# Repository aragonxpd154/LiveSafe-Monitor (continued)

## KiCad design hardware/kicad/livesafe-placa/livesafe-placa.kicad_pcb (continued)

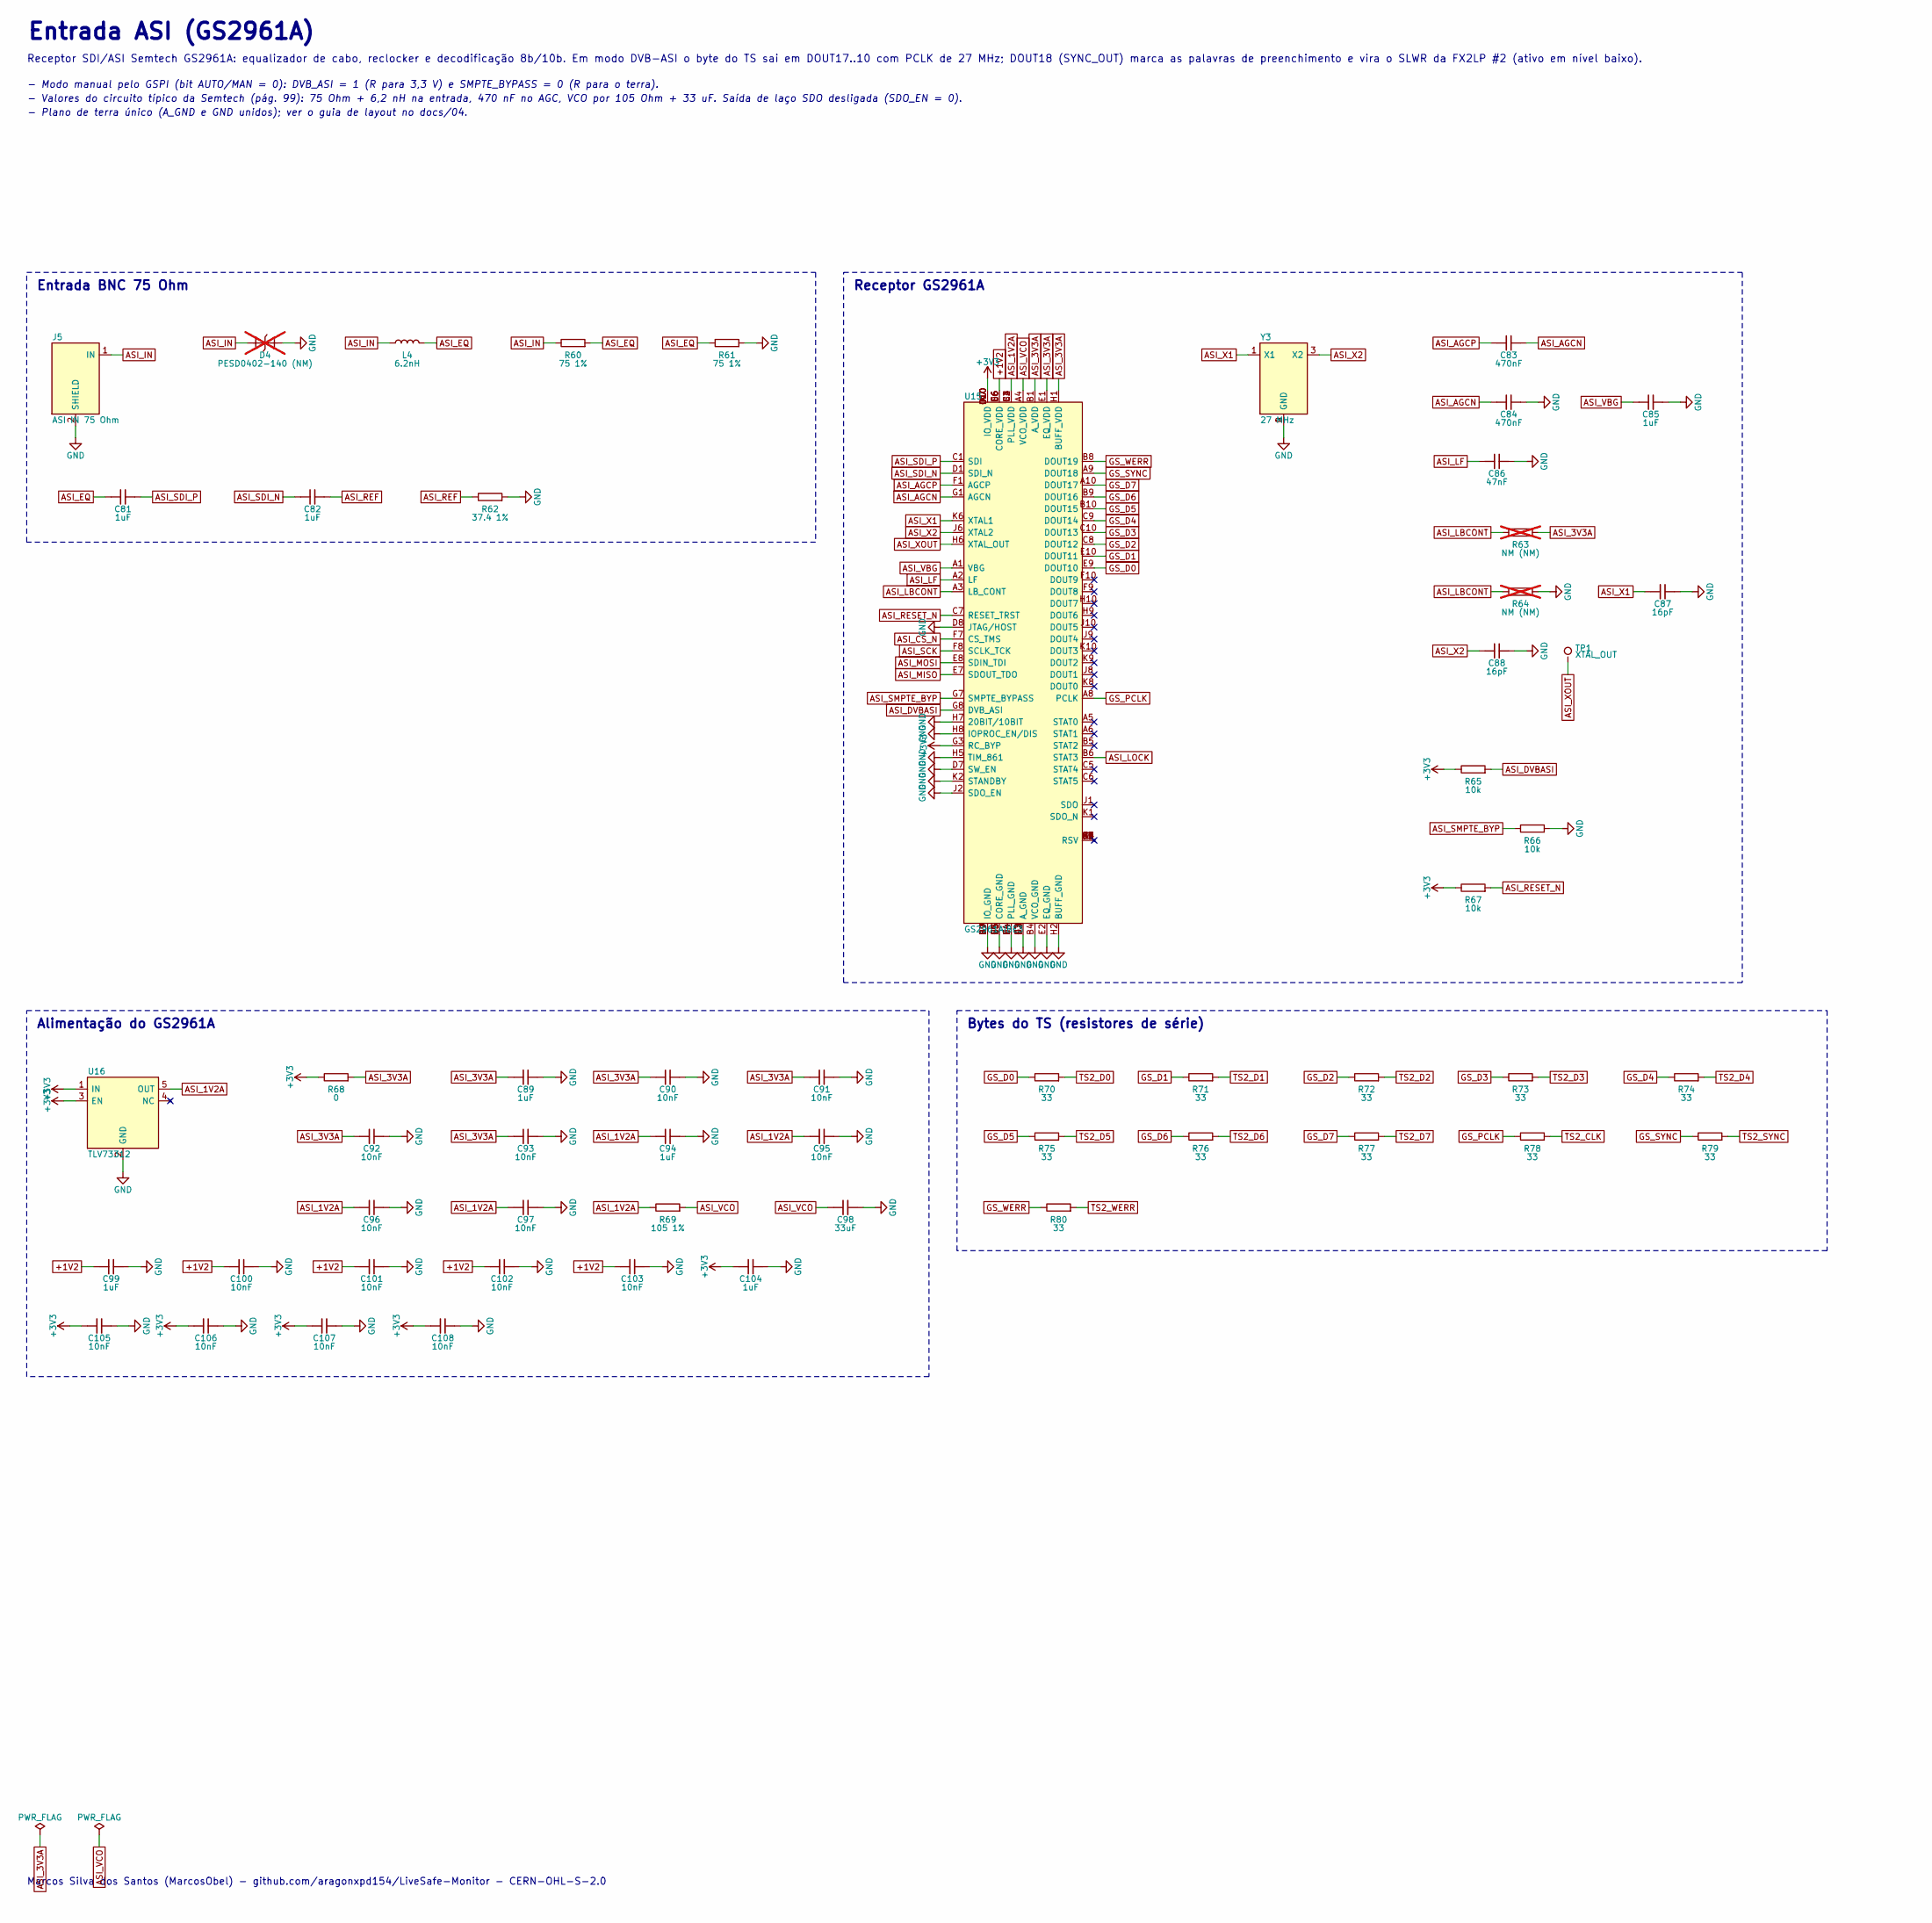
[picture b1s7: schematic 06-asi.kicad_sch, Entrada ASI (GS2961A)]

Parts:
C81, C82, C85, C89, C94, C99, C104: 1uF; C_0402_1005Metric; MPN CL05A105KA5NQNC; LCSC C52923
C83, C84: 470nF; C_0402_1005Metric; MPN CL05A474KP5NNNC; LCSC C47339
C86: 47nF; C_0402_1005Metric; MPN CL05B473KO5NNNC; LCSC C307434
C87, C88: 16pF; C_0402_1005Metric; MPN 0402CG160J500NT; LCSC C48836
C90, C91, C92, C93, C95, C96, C97, C100, C101, C102, C103, C105, C106, C107, C108: 10nF; C_0402_1005Metric; MPN CL05B103KB5NNNC; LCSC C15195
C98: 33uF; C_1206_3216Metric; MPN C3216X5R1C336MTJ00N; LCSC C76658
D4: PESD0402-140 (NM); D_0402_1005Metric; MPN PESD0402-140; LCSC C10662; not fitted
J5: ASI IN 75 Ohm; BNC_Amphenol_B6252HB-NPP3G-50_Horizontal; MPN B6252HB-NPP3G-75
L4: 6.2nH; L_0402_1005Metric; MPN LQG15HS6N2S02D; LCSC C133049
R60, R61: 75 1%; R_0402_1005Metric; MPN 0402WGF750JTCE; LCSC C25133
R62: 37.4 1%; R_0402_1005Metric; MPN 0402WGF374JTCE; LCSC C25108
R63, R64: NM (NM); R_0402_1005Metric; not fitted
R65, R66, R67: 10k; R_0402_1005Metric; MPN 0402WGF1002TCE; LCSC C25744
R68: 0; R_0603_1608Metric; MPN 0603WAF0000T5E; LCSC C21189
R69: 105 1%; R_0402_1005Metric; MPN WR02X1050FTL; LCSC C367419
R70, R71, R72, R73, R74, R75, R76, R77, R78, R79, R80: 33; R_0402_1005Metric; MPN 0402WGF330JTCE; LCSC C25105
TP1: XTAL_OUT; TestPoint_Pad_D1.0mm
U15: GS2961AIBE3; BGA-100_11.0x11.0mm_Layout10x10_P1.0mm_Ball0.5mm_Pad0.4mm_N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; MPN GS2961AIBE3; LCSC C842837
U16: TLV73312; SOT-23-5; MPN TLV73312PDBVR; LCSC C473364
Y3: 27 MHz; Crystal_SMD_3225-4Pin_3.2x2.5mm; MPN X322527MOB4SI; LCSC C70595

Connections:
+1V2: C99.1, C100.1, C101.1, C102.1, C103.1, U15.D6 (CORE_VDD), U15.E6 (CORE_VDD), U15.F6 (CORE_VDD), U15.G6 (CORE_VDD); also elsewhere on the board
+3V3: C104.1, C105.1, C106.1, C107.1, C108.1, R65.1, R67.1, R68.1, U15.A7 (IO_VDD), U15.D10 (IO_VDD), U15.G3 (RC_BYP), U15.G10 (IO_VDD), U15.K7 (IO_VDD), U16.1 (IN), U16.3 (EN); also elsewhere on the board
ASI_1V2A: C94.1, C95.1, C96.1, C97.1, R69.1, U15.B2 (PLL_VDD), U15.C3 (PLL_VDD), U15.C4 (PLL_VDD), U16.5 (OUT)
ASI_3V3A: C89.1, C90.1, C91.1, C92.1, C93.1, R63.2, R68.2, U15.B1 (A_VDD), U15.E1 (EQ_VDD), U15.H1 (BUFF_VDD)
ASI_AGCN: C83.2, C84.1, U15.G1 (AGCN)
ASI_AGCP: C83.1, U15.F1 (AGCP)
ASI_CS_N: U15.F7 (CS_TMS); also elsewhere on the board
ASI_DVBASI: R65.2, U15.G8 (DVB_ASI)
ASI_EQ: C81.1, L4.2, R60.2, R61.1
ASI_IN: D4.1 (K), J5.1 (IN), L4.1, R60.1
ASI_LBCONT: R63.1, R64.1, U15.A3 (LB_CONT)
ASI_LF: C86.1, U15.A2 (LF)
ASI_LOCK: U15.B6 (STAT3); also elsewhere on the board
ASI_MISO: U15.E7 (SDOUT_TDO); also elsewhere on the board
ASI_MOSI: U15.E8 (SDIN_TDI); also elsewhere on the board
ASI_REF: C82.2, R62.1
ASI_RESET_N: R67.2, U15.C7 (RESET_TRST); also elsewhere on the board
ASI_SCK: U15.F8 (SCLK_TCK); also elsewhere on the board
ASI_SDI_N: C82.1, U15.D1 (SDI_N)
ASI_SDI_P: C81.2, U15.C1 (SDI)
ASI_SMPTE_BYP: R66.1, U15.G7 (SMPTE_BYPASS)
ASI_VBG: C85.1, U15.A1 (VBG)
ASI_VCO: C98.1, R69.2, U15.A4 (VCO_VDD)
ASI_X1: C87.1, U15.K6 (XTAL1), Y3.1 (X1)
ASI_X2: C88.1, U15.J6 (XTAL2), Y3.3 (X2)
ASI_XOUT: TP1.1, U15.H6 (XTAL_OUT)
GND: C84.2, C85.2, C86.2, C87.2, C88.2, C89.2, C90.2, C91.2, C92.2, C93.2, C94.2, C95.2, C96.2, C97.2, C98.2, C99.2, C100.2, C101.2, C102.2, C103.2, C104.2, C105.2, C106.2, C107.2, C108.2, D4.2 (A), J5.2 (SHIELD), R61.2, R62.2, R64.2, R66.2, U15.B4 (VCO_GND), U15.B7 (IO_GND), U15.C2 (A_GND), U15.D2 (A_GND), U15.D3 (A_GND), U15.D4 (PLL_GND), U15.D5 (CORE_GND), U15.D7 (SW_EN), U15.D8 (JTAG/HOST), U15.D9 (IO_GND), U15.E2 (EQ_GND), U15.E3 (A_GND), U15.E4 (PLL_GND), U15.E5 (CORE_GND), U15.F3 (A_GND), U15.F4 (PLL_GND), U15.F5 (CORE_GND), U15.G2 (A_GND), U15.G4 (CORE_GND), U15.G5 (CORE_GND), U15.G9 (IO_GND), U15.H2 (BUFF_GND), U15.H3 (CORE_GND), U15.H5 (TIM_861), U15.H7 (20BIT/10BIT), U15.H8 (IOPROC_EN/DIS), U15.J2 (SDO_EN), U15.J7 (IO_GND), U15.K2 (STANDBY), U16.2 (GND), Y3.2 (GND), Y3.4 (GND); also elsewhere on the board
GS_D0: R70.1, U15.E9 (DOUT10)
GS_D1: R71.1, U15.E10 (DOUT11)
GS_D2: R72.1, U15.C8 (DOUT12)
GS_D3: R73.1, U15.C10 (DOUT13)
GS_D4: R74.1, U15.C9 (DOUT14)
GS_D5: R75.1, U15.B10 (DOUT15)
GS_D6: R76.1, U15.B9 (DOUT16)
GS_D7: R77.1, U15.A10 (DOUT17)
GS_PCLK: R78.1, U15.A8 (PCLK)
GS_SYNC: R79.1, U15.A9 (DOUT18)
GS_WERR: R80.1, U15.B8 (DOUT19)
TS2_CLK: R78.2; also elsewhere on the board
TS2_D0: R70.2; also elsewhere on the board
TS2_D1: R71.2; also elsewhere on the board
TS2_D2: R72.2; also elsewhere on the board
TS2_D3: R73.2; also elsewhere on the board
TS2_D4: R74.2; also elsewhere on the board
TS2_D5: R75.2; also elsewhere on the board
TS2_D6: R76.2; also elsewhere on the board
TS2_D7: R77.2; also elsewhere on the board
TS2_SYNC: R79.2; also elsewhere on the board
TS2_WERR: R80.2; also elsewhere on the board

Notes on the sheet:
Entrada BNC 75 Ohm
Receptor GS2961A
Alimentação do GS2961A
Bytes do TS (resistores de série)
Entrada ASI (GS2961A)
Receptor SDI/ASI Semtech GS2961A: equalizador de cabo, reclocker e decodificação 8b/10b. Em modo DVB-ASI o byte do TS sai em DOUT17..10 com PCLK de 27 MHz; DOUT18 (SYNC_OUT) marca as palavras de preenchimento e vira o SLWR da FX2LP #2 (ativo em nível baixo).
- Modo manual pelo GSPI (bit AUTO/MAN = 0): DVB_ASI = 1 (R para 3,3 V) e SMPTE_BYPASS = 0 (R para o terra).
- Valores do circuito típico da Semtech (pág. 99): 75 Ohm + 6,2 nH na entrada, 470 nF no AGC, VCO por 105 Ohm + 33 uF. Saída de laço SDO desligada (SDO_EN = 0).
- Plano de terra único (A_GND e GND unidos); ver o guia de layout no docs/04.
Marcos Silva dos Santos (MarcosObel) - github.com/aragonxpd154/LiveSafe-Monitor - CERN-OHL-S-2.0

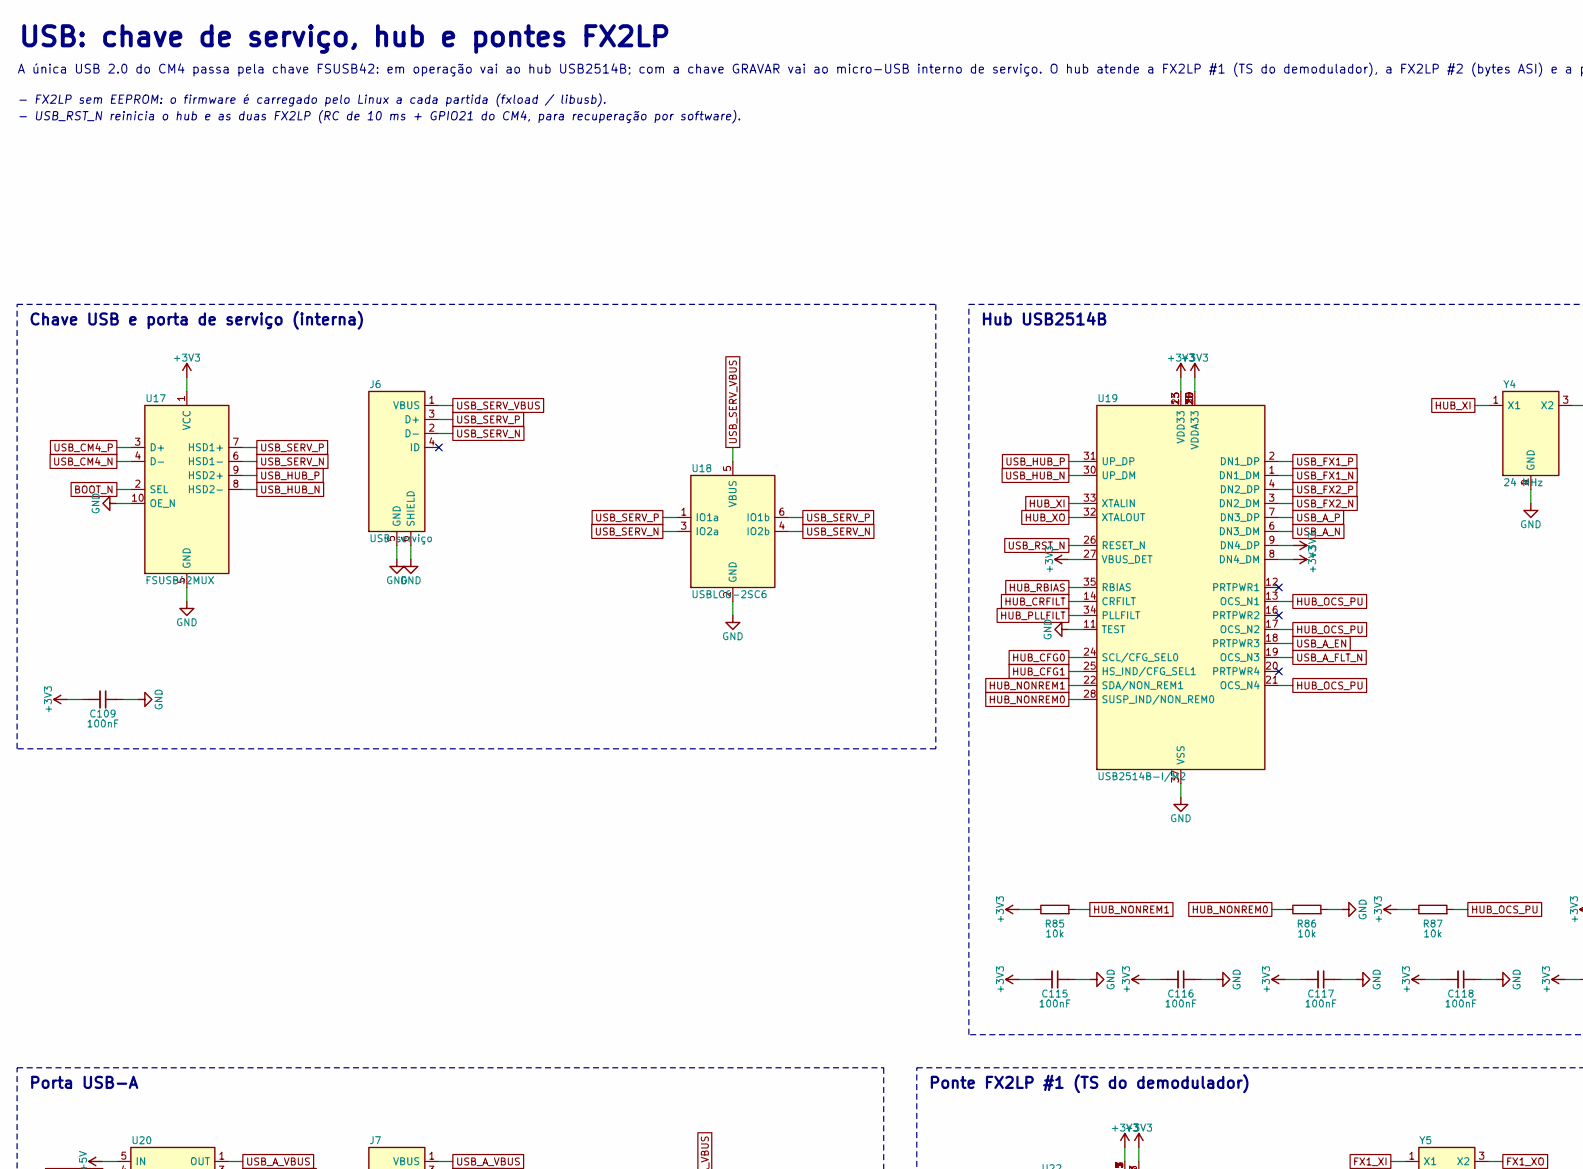
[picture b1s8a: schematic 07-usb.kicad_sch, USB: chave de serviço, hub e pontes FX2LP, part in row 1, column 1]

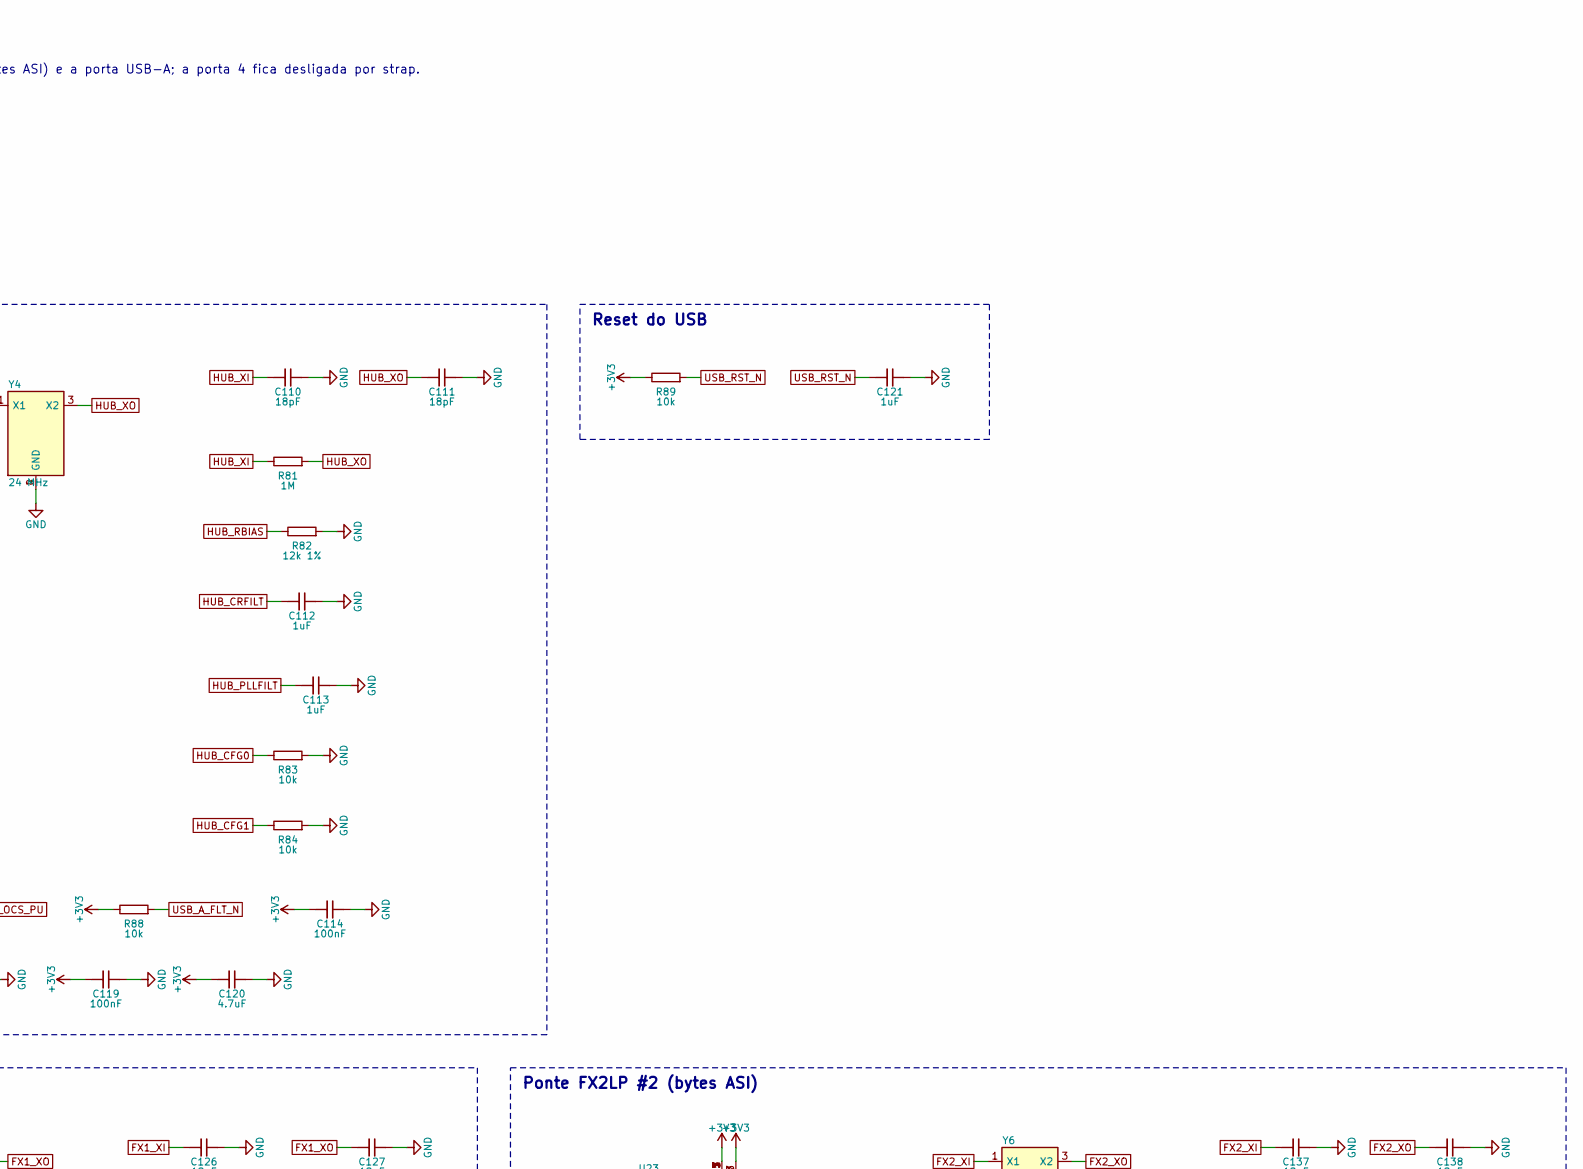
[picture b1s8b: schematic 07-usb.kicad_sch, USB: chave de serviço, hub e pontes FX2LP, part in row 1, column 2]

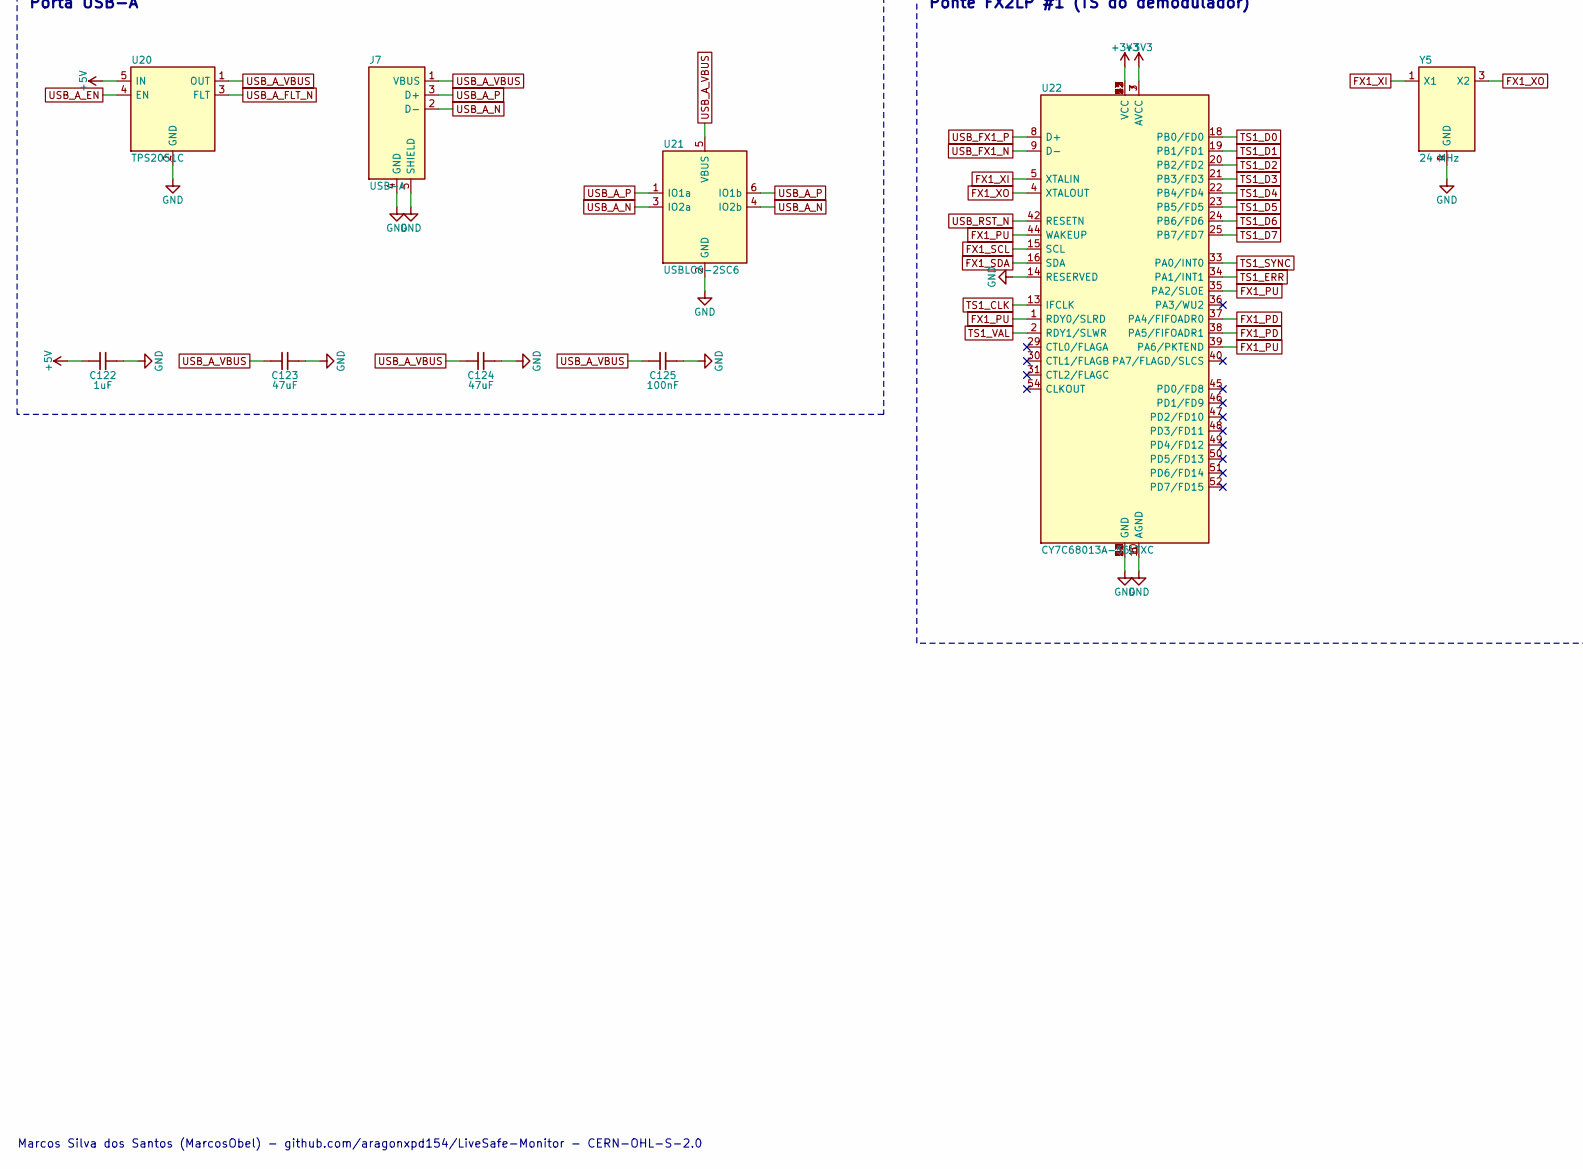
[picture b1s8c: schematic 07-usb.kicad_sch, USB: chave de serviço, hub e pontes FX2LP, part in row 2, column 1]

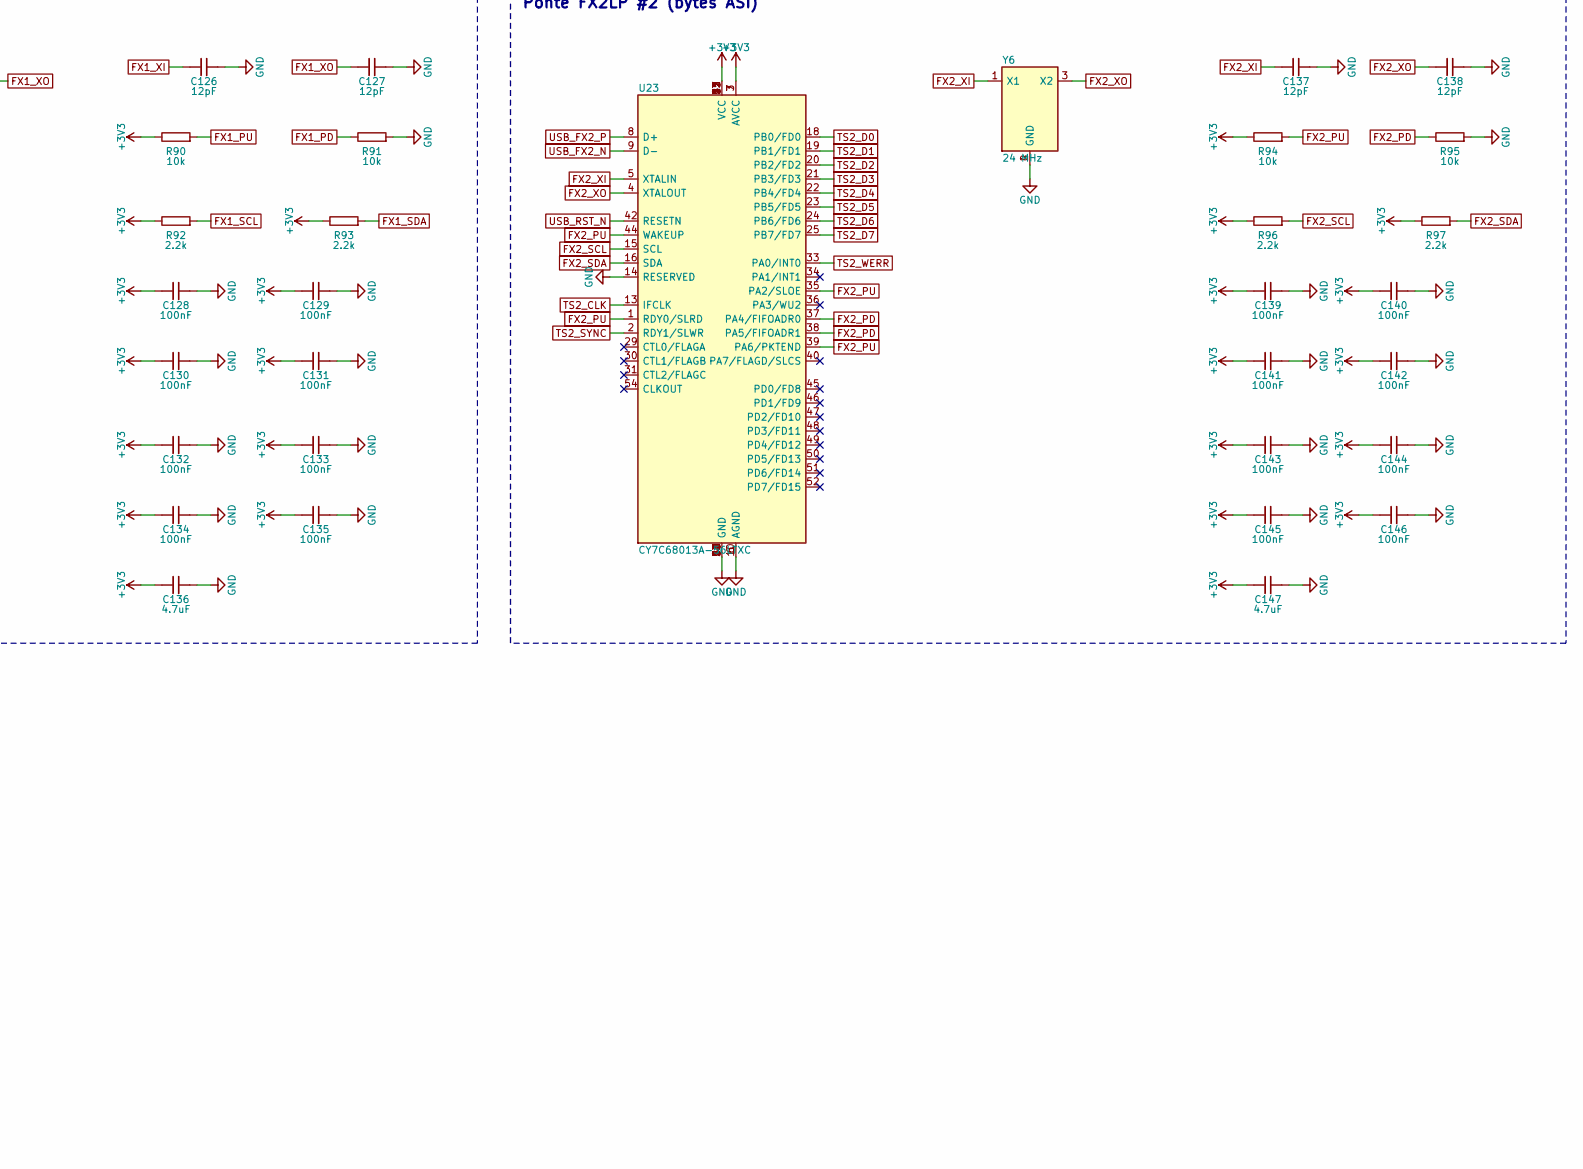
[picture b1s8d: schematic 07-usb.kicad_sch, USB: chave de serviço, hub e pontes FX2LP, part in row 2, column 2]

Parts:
C109, C114, C115, C116, C117, C118, C119, C125, C128, C129, C130, C131, C132, C133, C134, C135, C139, C140, C141, C142, C143, C144, C145, C146: 100nF; C_0402_1005Metric; MPN CL05B104KO5NNNC; LCSC C1525
C110, C111: 18pF; C_0402_1005Metric; MPN CL05C180JB5NNNC; LCSC C307443
C112, C113, C121, C122: 1uF; C_0402_1005Metric; MPN CL05A105KA5NQNC; LCSC C52923
C120, C136, C147: 4.7uF; C_0603_1608Metric; MPN CL10A475KO8NNNC; LCSC C19666
C123, C124: 47uF; C_1206_3216Metric; MPN CL31A476MPHNNNE; LCSC C96123
C126, C127, C137, C138: 12pF; C_0402_1005Metric; MPN CL05C120JB5NNNC; LCSC C26406
J6: USB serviço; USB_Micro-B_Wuerth_614105150721_Vertical; MPN 614105150721
J7: USB-A; USB_A_Molex_67643_Horizontal; MPN 67643-0910
R81: 1M; R_0402_1005Metric; MPN 0402WGF1004TCE; LCSC C26083
R82: 12k 1%; R_0402_1005Metric; MPN 0402WGF1202TCE; LCSC C25752
R83, R84, R85, R86, R87, R88, R89, R90, R91, R94, R95: 10k; R_0402_1005Metric; MPN 0402WGF1002TCE; LCSC C25744
R92, R93, R96, R97: 2.2k; R_0402_1005Metric; MPN 0402WGF2201TCE; LCSC C25879
U17: FSUSB42MUX; MSOP-10_3x3mm_P0.5mm; MPN FSUSB42MUX; LCSC C11355
U18, U21: USBLC6-2SC6; SOT-23-6; MPN USBLC6-2SC6; LCSC C7519
U19: USB2514B-I/M2; QFN-36-1EP_6x6mm_P0.5mm_EP3.7x3.7mm; MPN USB2514B-I/M2; LCSC C220679
U20: TPS2051C; SOT-23-5; MPN TPS2051CDBVR; LCSC C129581
U22, U23: CY7C68013A-56LTXC; QFN-56-1EP_8x8mm_P0.5mm_EP4.5x5.2mm; MPN CY7C68013A-56LTXC; LCSC C14912
Y4, Y5, Y6: 24 MHz; Crystal_SMD_3225-4Pin_3.2x2.5mm; MPN X322524MOB4SI; LCSC C70590

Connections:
+3V3: C109.1, C114.1, C115.1, C116.1, C117.1, C118.1, C119.1, C120.1, C128.1, C129.1, C130.1, C131.1, C132.1, C133.1, C134.1, C135.1, C136.1, C139.1, C140.1, C141.1, C142.1, C143.1, C144.1, C145.1, C146.1, C147.1, R85.1, R87.1, R88.1, R89.1, R90.1, R92.1, R93.1, R94.1, R96.1, R97.1, U17.1 (VCC), U19.5 (VDDA33), U19.8 (DN4_DM), U19.9 (DN4_DP), U19.10 (VDDA33), U19.15 (VDD33), U19.23 (VDD33), U19.27 (VBUS_DET), U19.29 (VDDA33), U19.36 (VDDA33), U22.3 (AVCC), U22.7 (AVCC), U22.11 (VCC), U22.17 (VCC), U22.27 (VCC), U22.32 (VCC), U22.43 (VCC), U22.55 (VCC), U23.3 (AVCC), U23.7 (AVCC), U23.11 (VCC), U23.17 (VCC), U23.27 (VCC), U23.32 (VCC), U23.43 (VCC), U23.55 (VCC); also elsewhere on the board
+5V: C122.1, U20.5 (IN); also elsewhere on the board
BOOT_N: U17.2 (SEL); also elsewhere on the board
FX1_PD: R91.1, U22.37 (PA4/FIFOADR0), U22.38 (PA5/FIFOADR1)
FX1_PU: R90.2, U22.1 (RDY0/SLRD), U22.35 (PA2/SLOE), U22.39 (PA6/PKTEND), U22.44 (WAKEUP)
FX1_SCL: R92.2, U22.15 (SCL)
FX1_SDA: R93.2, U22.16 (SDA)
FX1_XI: C126.1, U22.5 (XTALIN), Y5.1 (X1)
FX1_XO: C127.1, U22.4 (XTALOUT), Y5.3 (X2)
FX2_PD: R95.1, U23.37 (PA4/FIFOADR0), U23.38 (PA5/FIFOADR1)
FX2_PU: R94.2, U23.1 (RDY0/SLRD), U23.35 (PA2/SLOE), U23.39 (PA6/PKTEND), U23.44 (WAKEUP)
FX2_SCL: R96.2, U23.15 (SCL)
FX2_SDA: R97.2, U23.16 (SDA)
FX2_XI: C137.1, U23.5 (XTALIN), Y6.1 (X1)
FX2_XO: C138.1, U23.4 (XTALOUT), Y6.3 (X2)
GND: C109.2, C110.2, C111.2, C112.2, C113.2, C114.2, C115.2, C116.2, C117.2, C118.2, C119.2, C120.2, C121.2, C122.2, C123.2, C124.2, C125.2, C126.2, C127.2, C128.2, C129.2, C130.2, C131.2, C132.2, C133.2, C134.2, C135.2, C136.2, C137.2, C138.2, C139.2, C140.2, C141.2, C142.2, C143.2, C144.2, C145.2, C146.2, C147.2, J6.5 (GND), J6.6 (SHIELD), J7.4 (GND), J7.5 (SHIELD), R82.2, R83.2, R84.2, R86.2, R91.2, R95.2, U17.5 (GND), U17.10 (OE_N), U18.2 (GND), U19.11 (TEST), U19.37 (VSS), U20.2 (GND), U21.2 (GND), U22.6 (AGND), U22.10 (AGND), U22.12 (GND), U22.14 (RESERVED), U22.26 (GND), U22.28 (GND), U22.41 (GND), U22.53 (GND), U22.56 (GND), U22.57 (GND), U23.6 (AGND), U23.10 (AGND), U23.12 (GND), U23.14 (RESERVED), U23.26 (GND), U23.28 (GND), U23.41 (GND), U23.53 (GND), U23.56 (GND), U23.57 (GND), Y4.2 (GND), Y4.4 (GND), Y5.2 (GND), Y5.4 (GND), Y6.2 (GND), Y6.4 (GND); also elsewhere on the board
HUB_CFG0: R83.1, U19.24 (SCL/CFG_SEL0)
HUB_CFG1: R84.1, U19.25 (HS_IND/CFG_SEL1)
HUB_CRFILT: C112.1, U19.14 (CRFILT)
HUB_NONREM0: R86.1, U19.28 (SUSP_IND/NON_REM0)
HUB_NONREM1: R85.2, U19.22 (SDA/NON_REM1)
HUB_OCS_PU: R87.2, U19.13 (OCS_N1), U19.17 (OCS_N2), U19.21 (OCS_N4)
HUB_PLLFILT: C113.1, U19.34 (PLLFILT)
HUB_RBIAS: R82.1, U19.35 (RBIAS)
HUB_XI: C110.1, R81.1, U19.33 (XTALIN), Y4.1 (X1)
HUB_XO: C111.1, R81.2, U19.32 (XTALOUT), Y4.3 (X2)
TS1_CLK: U22.13 (IFCLK); also elsewhere on the board
TS1_D0: U22.18 (PB0/FD0); also elsewhere on the board
TS1_D1: U22.19 (PB1/FD1); also elsewhere on the board
TS1_D2: U22.20 (PB2/FD2); also elsewhere on the board
TS1_D3: U22.21 (PB3/FD3); also elsewhere on the board
TS1_D4: U22.22 (PB4/FD4); also elsewhere on the board
TS1_D5: U22.23 (PB5/FD5); also elsewhere on the board
TS1_D6: U22.24 (PB6/FD6); also elsewhere on the board
TS1_D7: U22.25 (PB7/FD7); also elsewhere on the board
TS1_ERR: U22.34 (PA1/INT1); also elsewhere on the board
TS1_SYNC: U22.33 (PA0/INT0); also elsewhere on the board
TS1_VAL: U22.2 (RDY1/SLWR); also elsewhere on the board
TS2_CLK: U23.13 (IFCLK); also elsewhere on the board
TS2_D0: U23.18 (PB0/FD0); also elsewhere on the board
TS2_D1: U23.19 (PB1/FD1); also elsewhere on the board
TS2_D2: U23.20 (PB2/FD2); also elsewhere on the board
TS2_D3: U23.21 (PB3/FD3); also elsewhere on the board
TS2_D4: U23.22 (PB4/FD4); also elsewhere on the board
TS2_D5: U23.23 (PB5/FD5); also elsewhere on the board
TS2_D6: U23.24 (PB6/FD6); also elsewhere on the board
TS2_D7: U23.25 (PB7/FD7); also elsewhere on the board
TS2_SYNC: U23.2 (RDY1/SLWR); also elsewhere on the board
TS2_WERR: U23.33 (PA0/INT0); also elsewhere on the board
USB_A_EN: U19.18 (PRTPWR3), U20.4 (EN)
USB_A_FLT_N: R88.2, U19.19 (OCS_N3), U20.3 (FLT)
USB_A_N: J7.2 (D-), U19.6 (DN3_DM), U21.3 (IO2a), U21.4 (IO2b)
USB_A_P: J7.3 (D+), U19.7 (DN3_DP), U21.1 (IO1a), U21.6 (IO1b)
USB_A_VBUS: C123.1, C124.1, C125.1, J7.1 (VBUS), U20.1 (OUT), U21.5 (VBUS)
USB_CM4_N: U17.4 (D-); also elsewhere on the board
USB_CM4_P: U17.3 (D+); also elsewhere on the board
USB_FX1_N: U19.1 (DN1_DM), U22.9 (D-)
USB_FX1_P: U19.2 (DN1_DP), U22.8 (D+)
USB_FX2_N: U19.3 (DN2_DM), U23.9 (D-)
USB_FX2_P: U19.4 (DN2_DP), U23.8 (D+)
USB_HUB_N: U17.8 (HSD2-), U19.30 (UP_DM)
USB_HUB_P: U17.9 (HSD2+), U19.31 (UP_DP)
USB_RST_N: C121.1, R89.2, U19.26 (RESET_N), U22.42 (RESETN), U23.42 (RESETN); also elsewhere on the board
USB_SERV_N: J6.2 (D-), U17.6 (HSD1-), U18.3 (IO2a), U18.4 (IO2b)
USB_SERV_P: J6.3 (D+), U17.7 (HSD1+), U18.1 (IO1a), U18.6 (IO1b)
USB_SERV_VBUS: J6.1 (VBUS), U18.5 (VBUS)

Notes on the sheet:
Chave USB e porta de serviço (interna)
Hub USB2514B
Reset do USB
Porta USB-A
Ponte FX2LP #1 (TS do demodulador)
Ponte FX2LP #2 (bytes ASI)
USB: chave de serviço, hub e pontes FX2LP
A única USB 2.0 do CM4 passa pela chave FSUSB42: em operação vai ao hub USB2514B; com a chave GRAVAR vai ao micro-USB interno de serviço. O hub atende a FX2LP #1 (TS do demodulador), a FX2LP #2 (bytes ASI) e a porta USB-A; a porta 4 fica desligada por strap.
- FX2LP sem EEPROM: o firmware é carregado pelo Linux a cada partida (fxload / libusb).
- USB_RST_N reinicia o hub e as duas FX2LP (RC de 10 ms + GPIO21 do CM4, para recuperação por software).
Marcos Silva dos Santos (MarcosObel) - github.com/aragonxpd154/LiveSafe-Monitor - CERN-OHL-S-2.0

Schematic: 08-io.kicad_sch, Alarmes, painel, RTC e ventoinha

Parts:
BT1: CR1220; BatteryHolder_Keystone_3000_1x12mm; MPN 3000; LCSC C238097
C148: 10uF; C_0603_1608Metric; MPN CL10A106KP8NNNC; LCSC C19702
C149, C150, C151: 100nF; C_0402_1005Metric; MPN CL05B104KO5NNNC; LCSC C1525
D5, D6, D7, D8: 1N4148W; D_SOD-123; MPN 1N4148W-7-F; LCSC C83528
D9, D10, D11, D12: amarelo; LED_0603_1608Metric; MPN 19-217/Y5C-AM1N1VY/3T; LCSC C282130
D13: verde; LED_0603_1608Metric; MPN 19-217/GHC-YR1S2/3T; LCSC C72043
D14: vermelho; LED_0603_1608Metric; MPN 19-217/R6C-AL1M2VY/3T; LCSC C72044
D15: verde (PWR); LED_0603_1608Metric; MPN 19-217/GHC-YR1S2/3T; LCSC C72043
D16: amarelo (ACT); LED_0603_1608Metric; MPN 19-217/Y5C-AM1N1VY/3T; LCSC C282130
D17: BAT54C; SOT-23; MPN BAT54C,215; LCSC C37704
F2: 0,1 A; Fuse_1812_4532Metric; MPN 1812L010/60DR; LCSC C207062
J8: ENTRADAS; PhoenixContact_MC_1,5_6-G-3.81_1x06_P3.81mm_Horizontal; MPN MC 1,5/6-G-3,81
J9: RELÉS; PhoenixContact_MC_1,5_12-G-3.81_1x12_P3.81mm_Horizontal; MPN MC 1,5/12-G-3,81
J10: VENTOINHA 12 V; Molex_KK-254_AE-6410-04A_1x04_P2.54mm_Vertical; MPN 22-27-2041
J11: CONSOLE; PinHeader_1x03_P2.54mm_Vertical; MPN PZ254V-11-03P; LCSC C2937625
K1, K2, K3, K4: G5V-1 5V; Relay_SPDT_Omron_G5V-1; MPN G5V-1 DC5; LCSC C28695
R98, R100, R102, R104: 3.3k; R_1206_3216Metric; MPN 1206W4F3301T5E; LCSC C26032
R99, R101, R103, R105, R107, R109, R111, R113, R118: 10k; R_0402_1005Metric; MPN 0402WGF1002TCE; LCSC C25744
R106, R108, R110, R112, R116, R117: 1k; R_0402_1005Metric; MPN 0402WGF1001TCE; LCSC C11702
R114, R115: 330; R_0402_1005Metric; MPN 0402WGF3300TCE; LCSC C25104
U24, U25, U26, U27: LTV-817S; SMDIP-4_W9.53mm; MPN LTV-817S; LCSC C189217
U28: ULN2003A; SOIC-16_3.9x9.9mm_P1.27mm; MPN ULN2003ADR; LCSC C7512
U29: PCF85063A; DFN-10-1EP_2.6x2.6mm_P0.5mm_EP1.3x2.2mm; MPN PCF85063ATL/1,118; LCSC C404360
U30: EMC2301; MSOP-8_3x3mm_P0.65mm; MPN EMC2301-1-ACZL-TR; LCSC C148036
Y7: 32.768 kHz; Crystal_SMD_2012-2Pin_2.0x1.2mm; MPN FC-12M 32.7680KA-A3; LCSC C1985290

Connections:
+3V3: C151.1, D17.1 (A1), R99.1, R101.1, R103.1, R105.1, R118.1, U30.3 (VDD); also elsewhere on the board
+5V: C148.1, C149.1, K1.2 (COIL+), K2.2 (COIL+), K3.2 (COIL+), K4.2 (COIL+), R106.1, R108.1, R110.1, R112.1, U28.9 (COM); also elsewhere on the board
+12V: F2.1, J10.2 (+12V); also elsewhere on the board
+12V_AUX: F2.2, J8.6
CM4_3V3: R116.1, R117.1; also elsewhere on the board
CON_RX: J11.3; also elsewhere on the board
CON_TX: J11.2; also elsewhere on the board
FAN_PWM: J10.4 (PWM), U30.5 (PWM)
FAN_TACH: J10.3 (TACH), R118.2, U30.6 (TACH)
GND: BT1.2 (-), C148.2, C149.2, C150.2, C151.2, D13.1 (K), D14.1 (K), J10.1 (GND), J11.1, R107.2, R109.2, R111.2, R113.2, U24.3 (E), U25.3 (E), U26.3 (E), U27.3 (E), U28.5 (I5), U28.6 (I6), U28.7 (I7), U28.8 (GND), U29.3 (CLKOE), U29.5 (VSS), U29.11 (VSS), U30.4 (GND), U30.7 (CLK); also elsewhere on the board
GPI1: R99.2, U24.4 (C); also elsewhere on the board
GPI2: R101.2, U25.4 (C); also elsewhere on the board
GPI3: R103.2, U26.4 (C); also elsewhere on the board
GPI4: R105.2, U27.4 (C); also elsewhere on the board
GPO1: R107.1, U28.1 (I1); also elsewhere on the board
GPO2: R109.1, U28.2 (I2); also elsewhere on the board
GPO3: R111.1, U28.3 (I3); also elsewhere on the board
GPO4: R113.1, U28.4 (I4); also elsewhere on the board
I2C0_SCL: U29.7 (SCL), U30.2 (SCL); also elsewhere on the board
I2C0_SDA: U29.6 (SDA), U30.1 (SDA); also elsewhere on the board
IN1_P: J8.1, R98.1
IN2_P: J8.2, R100.1
IN3_P: J8.3, R102.1
IN4_P: J8.4, R104.1
IN_COM: D5.2 (A), D6.2 (A), D7.2 (A), D8.2 (A), J8.5, U24.2 (K), U25.2 (K), U26.2 (K), U27.2 (K)
K1_DRV: D9.1 (K), K1.9 (COIL-), U28.16 (O1)
K1_LED: D9.2 (A), R106.2
K2_DRV: D10.1 (K), K2.9 (COIL-), U28.15 (O2)
K2_LED: D10.2 (A), R108.2
K3_DRV: D11.1 (K), K3.9 (COIL-), U28.14 (O3)
K3_LED: D11.2 (A), R110.2
K4_DRV: D12.1 (K), K4.9 (COIL-), U28.13 (O4)
K4_LED: D12.2 (A), R112.2
LED_ACT_A: D16.2 (A), R117.2
LED_ACT_N: D16.1 (K); also elsewhere on the board
LED_ALM: R115.1; also elsewhere on the board
LED_ALM_A: D14.2 (A), R115.2
LED_OK: R114.1; also elsewhere on the board
LED_OK_A: D13.2 (A), R114.2
LED_PWR_A: D15.2 (A), R116.2
LED_PWR_N: D15.1 (K); also elsewhere on the board
OPTO1_A: D5.1 (K), R98.2, U24.1 (A)
OPTO2_A: D6.1 (K), R100.2, U25.1 (A)
OPTO3_A: D7.1 (K), R102.2, U26.1 (A)
OPTO4_A: D8.1 (K), R104.2, U27.1 (A)
RLY1_C: J9.1, K1.5 (COM), K1.6 (COM)
RLY1_NA: J9.2, K1.10 (NO)
RLY1_NF: J9.3, K1.1 (NC)
RLY2_C: J9.4, K2.5 (COM), K2.6 (COM)
RLY2_NA: J9.5, K2.10 (NO)
RLY2_NF: J9.6, K2.1 (NC)
RLY3_C: J9.7, K3.5 (COM), K3.6 (COM)
RLY3_NA: J9.8, K3.10 (NO)
RLY3_NF: J9.9, K3.1 (NC)
RLY4_C: J9.10, K4.5 (COM), K4.6 (COM)
RLY4_NA: J9.11, K4.10 (NO)
RLY4_NF: J9.12, K4.1 (NC)
RTC_VDD: C150.1, D17.3 (K), U29.10 (VDD)
RTC_XI: U29.1 (OSCI), Y7.1 (X1)
RTC_XO: U29.2 (OSCO), Y7.2 (X2)
VBAT: BT1.1 (+), D17.2 (A2)

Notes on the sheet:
Entradas optoacopladas
Relés
LEDs do painel
Relógio de tempo real
Ventoinha
Console e fixação
Alarmes, painel, RTC e ventoinha
4 entradas optoacopladas com comum (12-24 V, ou contato seco usando o +12 V auxiliar), 4 relés SPDT para a remota do abrigo, LEDs do painel, relógio de tempo real com bateria, controle da ventoinha e console serial.
- Entrada ativa = GPIO em 0. Relé ligado = GPIO em 1 (ULN2003A).
- Borne J8: IN1 IN2 IN3 IN4 COM +12V(aux, 100 mA). Contato seco: ligar entre +12V(aux) e INx, com COM no GND; sinal externo de 12-24 V: INx positivo e COM negativo.
- Borne J9: C/NA/NF dos relés 1 a 4, nessa ordem.
Marcos Silva dos Santos (MarcosObel) - github.com/aragonxpd154/LiveSafe-Monitor - CERN-OHL-S-2.0
